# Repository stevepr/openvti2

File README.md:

# OpenVTI 2
----------------------------
The OpenVTI project implements a GPS based video time inserter for overlaying an accurate time stamp on each field of an analog video signal.  The OpenVTI device is an Arduino Mega 2560 single board computer along with a GPS receiver and a video overlay board.  This repository holds the Arduino source code.

## Building the OpenVTI software
---------------------------------
Prerequisites:
- Arduino IDE

## Building the OpenVTI hardware
------------------
The hardware:
- Arduino Mega 2560
- Gowoops GPS Module U-blox NEO-6M(Amazon: https://www.amazon.com/Gowoops-Module-Antenna-Arduino-Microcomputer/dp/B01MRNN3YZ)
- TinySine Video Overlay Shield using Max-7456

The source file pinconfig.h explains how to connect the GPS module and the TinySine board.

## Licensing
------------
 This program is free software: you can redistribute it and/or modify it under the terms of the GNU General Public License as published by the Free Software Foundation, either version 3 of the License, or (at your option) any later version.

 This program is distributed in the hope that it will be useful, but WITHOUT ANY WARRANTY; without even the implied warranty of MERCHANTABILITY or FITNESS FOR A PARTICULAR PURPOSE.  See the GNU General Public License for more details.

## Developers & Contributors
----------------------------
- Michael Fulbright
- Steve Preston

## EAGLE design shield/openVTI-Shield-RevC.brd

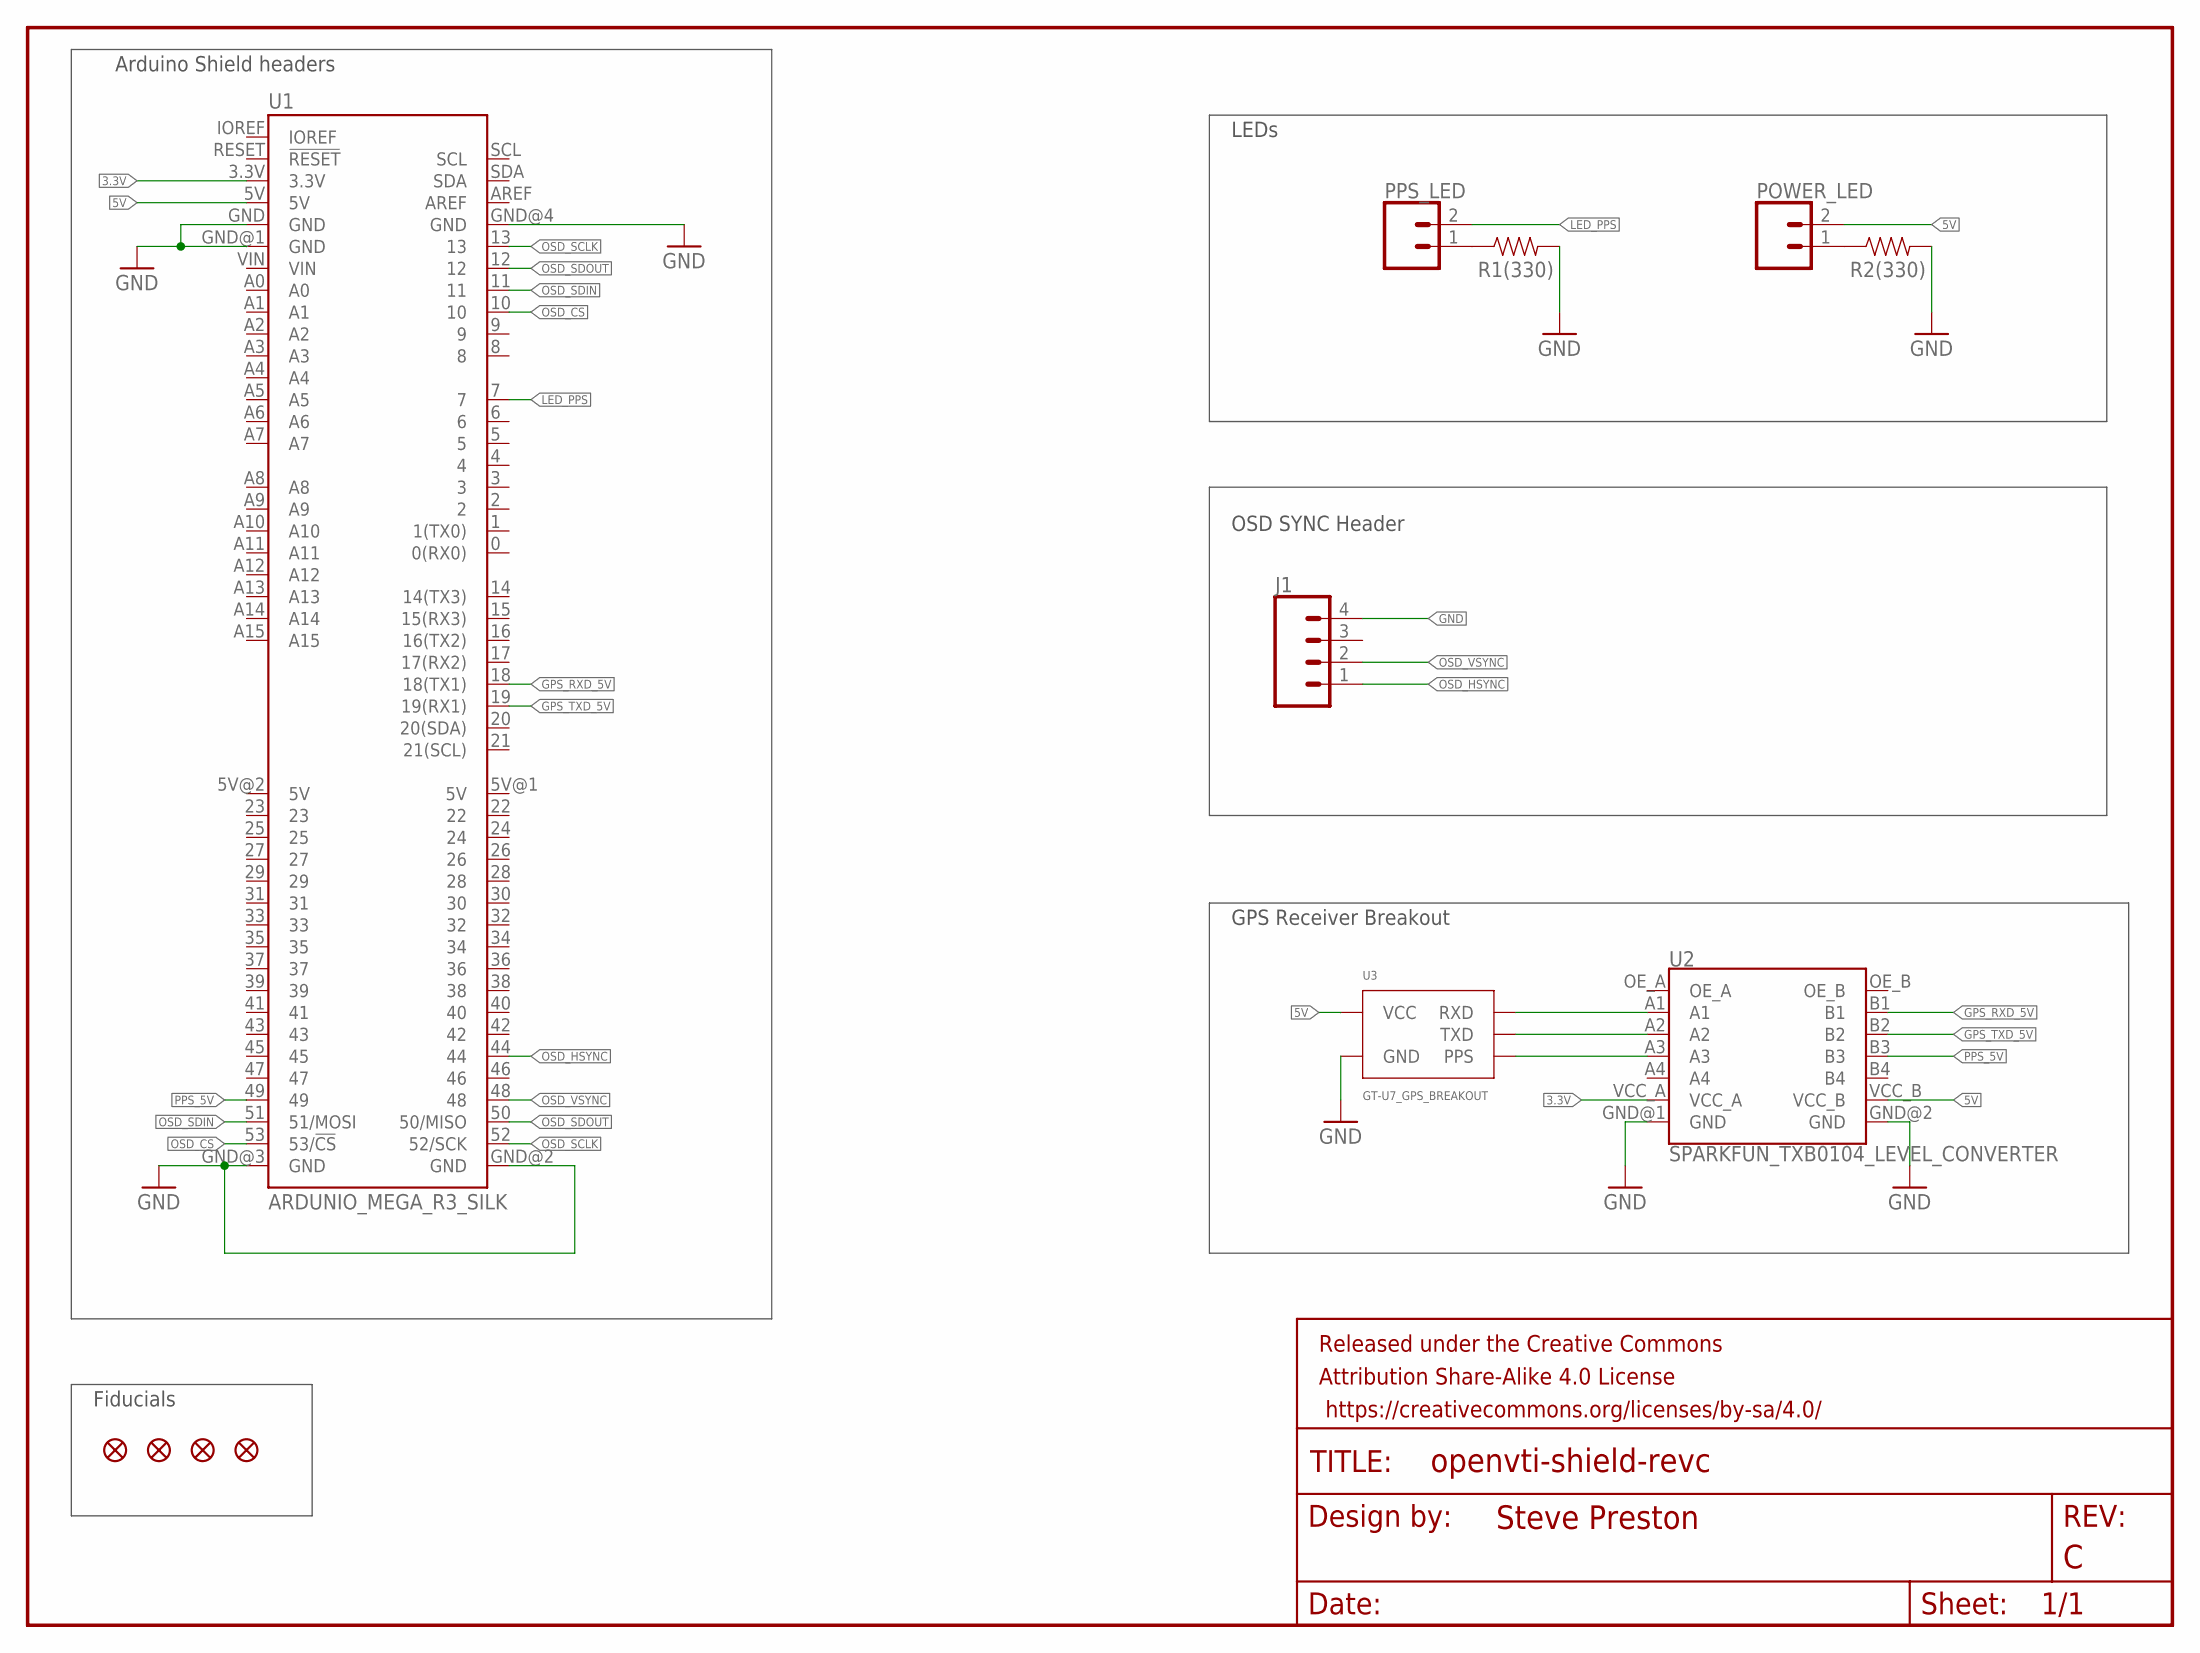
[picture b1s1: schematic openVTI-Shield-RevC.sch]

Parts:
FD1, FD2, FD3, FD4: FIDUCIALUFIDUCIAL; FIDUCIAL-MICRO
FRAME1: FRAME-LETTER; CREATIVE_COMMONS
J1: CONN_04PTH; 1X04
POWER_LED: CONN_02; 1X02
PPS_LED: CONN_02; 1X02
R1(330), R2(330): RESISTORAXIAL-0.3; AXIAL-0.3
U1: ARDUNIO_MEGA_R3_SILK; ARDUINO_MEGA_SILK
U2: SPARKFUN_TXB0104_LEVEL_CONVERTER; TXB0104_LEVEL_CONVERTER
U3: GT-U7_GPS_BREAKOUT; GT-UT

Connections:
3.3V: U1.3.3V, U2.VCC_A
5V: POWER_LED.2, U1.5V, U2.VCC_B, U3.VCC
GND: J1.4, R1(330).P$2 (2), R2(330).P$2 (2), U1.GND, U1.GND@1 (GND), U1.GND@2 (GND), U1.GND@3 (GND), U1.GND@4 (GND), U2.GND@1 (GND), U2.GND@2 (GND), U3.GND
GPS_RXD: U2.A1, U3.RXD
GPS_RXD_5V: U1.18 (18(TX1)), U2.B1
GPS_TXD: U2.A2, U3.TXD
GPS_TXD_5V: U1.19 (19(RX1)), U2.B2
LED_PPS: PPS_LED.2, U1.7
unnamed: PPS_LED.1, R1(330).P$1 (1)
unnamed: POWER_LED.1, R2(330).P$1 (1)
OSD_CS: U1.10, U1.53 (53/!CS)
OSD_HSYNC: J1.1, U1.44
OSD_SCLK: U1.13, U1.52 (52/SCK)
OSD_SDIN: U1.11, U1.51 (51/MOSI)
OSD_SDOUT: U1.12, U1.50 (50/MISO)
OSD_VSYNC: J1.2, U1.48
PPS: U2.A3, U3.PPS
PPS_5V: U1.49, U2.B3

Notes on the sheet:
LEDs
Arduino Shield headers
GPS Receiver Breakout
Fiducials
OSD SYNC Header

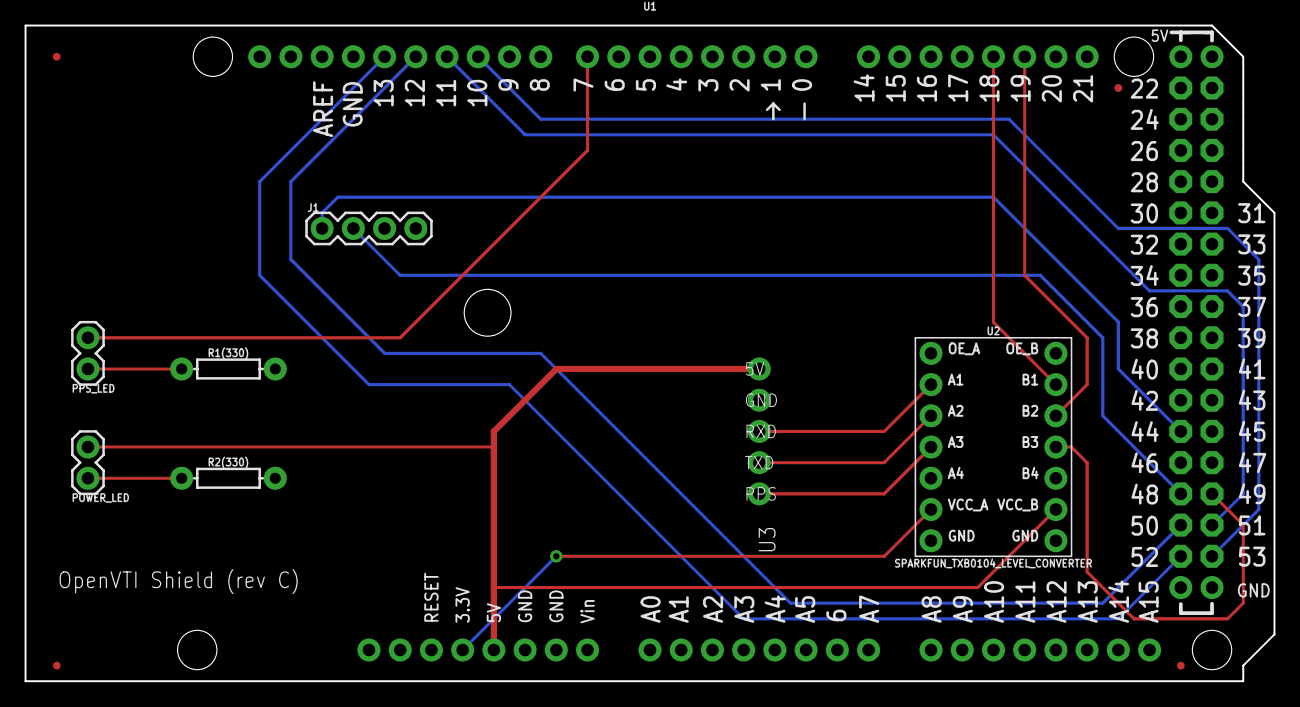
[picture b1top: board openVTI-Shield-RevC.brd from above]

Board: 2 copper layers, 101.6 x 53.3 mm, 13 parts (0 on the bottom side), 18 nets.

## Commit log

2017-10-25 :tada: Added .gitattributes & .gitignore files
2017-10-25 Start
2017-10-25 change to ultodec
2017-10-25 BottomRow
    Added Bottom row, removed test counters, added delay before starting
    overlay
2017-10-27 PPS
    Added pps int
2017-10-27 PPS + ultodec
2017-10-27 PPS ticks
    Fixed bug with FieldParity (field 1 start lengthened to 20ms and =
    changed to ==)
2017-10-28 GPSinit
    GPS init testing ready
2017-10-28 PPS working
    pps finally works and matches IOTA VTI
    - fixed EICRA bit initialization
2017-11-01 GPS serial test 2
    not quite working... display flakes out after a while
2017-11-02 gps serial test 2
    fixed issues with init, removed hsync int
2017-11-02 GPS serial test 2
    no readGPS & OSD.write
    no glitch after 40k fields...
2017-11-02 test 3
    problem is sendArray - maybe too fast
2017-11-02 Test 4
    writeArray seems to solve the issue. Might be timing.
2017-11-02 sendArray fixes
2017-11-02 another sendArray fix
    cleanup up logic for inAutoincrement and added write of 0xFF to actually
    turn if OFF after transferring array
2017-11-02 more mods to sendArray
2017-11-04 Stability test 1
    lots of fixes. leaving in some optional code before cleanup. will run
    this version for an extended time to see if the display dies.
2017-11-04 Clean-up
    Remove several bits of test code and other unused code
2017-11-04 Field Detection
    Re-enabled startup field detection logic
2017-11-05 int time values
2017-11-06 PPS sync working
2017-11-07 GPS state testing
2017-11-07 added top line but OSD dies again...
2017-11-07 ifdefs around toprow code
2017-11-07 test stackspace in atomax
2017-11-07 backed out testing of stack depth
2017-11-10 Beta
    should be worthy of more testing
2017-11-16 Field Detection
    Moved VSYNC to ICP1 input and better field detection logic
2017-11-20 Leap Seconds
    Add leap second to rotation
2017-11-20 PAL support
    Added support for PAL
2017-11-20 cleanup
2017-11-20 Revise field detection logic
2018-09-03 updated comments
2018-09-07 Clean up & bug fixes
    * re-organized state logic
    * fix some possible race conditions
    * add more error checking
    * clean-up
    * added documentation
    * added GPL header
2018-09-07 GPS/UTC update fix
    fix logic for switching from GPS to UTC time
2018-09-07 more error checking
2018-09-08 PUBX04 PPS test
    Added code to compare internal time to PUBX04 sentence and flag errors
2018-09-08 pps_now fix
2018-09-08 Add ave pps interval
2018-09-11 Fix PPS statistics
2018-09-12 Mega2560 version
    Port to Mega2560
2018-09-13 Fixed precision of time stamp
    time stamp was rounding off too much with integer math. Now matches IOTA-VTI within 0.2ms
2018-09-14 PPS & VSYNC commands
2018-09-15 added checksum, additions to document
2018-09-18 turn off testrow and one small fix
2019-01-21 NMEA OFF oommand
2019-10-01 Added extra check for consistency when transitioning from GPS to UTC time
2019-10-02 Initial version
2020-08-01 move echo of VSYNC time to AFTER int enabled
2020-09-13 Updated design doc
2020-09-24 fixed error in checking time at 0hrs UT when based on GPS time
2020-09-24 updated displayed version to 6.0
2020-09-25 fixed overflow of int when checking PUBX time
2020-10-01 added debugging output to serial
2020-10-02 checkpoint
2020-10-02 checkpoint again also changed default setup to FULLSCREEN
2020-10-03 various changes may have fixed the "glitch" via increasing the size of the gps sentence area by 1
2020-10-04 Add PPS led
2020-10-25 turn off timepulse configuration during GPS init (may revise later).
2020-11-02 Updates for initializing the timepulse
2021-01-25 various updates
2021-01-27 Limit PPS duration check to Sync and TimeValid modes update documentation
2021-01-28 changes to code for checking interval between PPS signals
2021-01-29 Add Clock_Tolerance Change altitude display
2021-01-29 display local datum in altitude line
2021-01-29 fixed version message
2021-01-29 added code to configure the time pulse (but still needs testing on the other breakout boards)
2021-09-17 turn OFF timepulse configuration by default - until I can debug the TP5 command
2025-01-15 some cleanup of warnings new version number a few changes to handle situations with no video input
2025-03-06 Moved Video Input detection to Loop() routine to allow video to be added after power on of VTI
2025-03-23 added 3d print files for enclosure
2025-03-30 lowered white level down to 80% to avoid affecting the intensity of the incomming video signal (per email from Bob Jones)
2025-03-31 updated version number

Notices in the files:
parts and their libraries:
SparkFun-Aesthetics: Licensing: Creative Commons ShareAlike 4.0 International - https://creativecommons.org/licenses/by-sa/4.0
SparkFun-Aesthetics: Released under the Creative Commons Attribution Share-Alike 4.0 License
SparkFun-Aesthetics: https://creativecommons.org/licenses/by-sa/4.0
